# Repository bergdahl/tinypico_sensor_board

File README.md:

# tinypico_sensor_board

This is a small motherboard for the TinyPICO to connect sensors to a QWIIC/STEMMA QT or Grove connector.

It supports three different configurations for the voltage on the connectors, to suppport the maximum number of sensors.

 - 3.3V power - 3.3V signal
 - 5V power, 3.3V signal
 - 5V power, 5V signal

See the PDF file for configuration options.

# Schema

See the PDF file for schematics.

# PCB

Designfiles in EAGLE format can be found in the `PCB` folder. Gerber files can be found in the `PCB/Gerbers` folder.

# Firmwares

Firmware for connecting the sensors to MQTT is present in the `firmware` folder.

TODO: Add more firmware.

## Connectors

The QWIIC/Stemma QT port is connected to the default I2C pins of the TinyPICO, GPIO21 and GPIO22. 

The Grove connector is connected to GPIO4 and GPIO5, so to use I2C you need initialize it with `Wire.Begin(5, 4)`.

Note that the ESP32 allows you to assign any function to any pin, so any communication type is possible, like UART.

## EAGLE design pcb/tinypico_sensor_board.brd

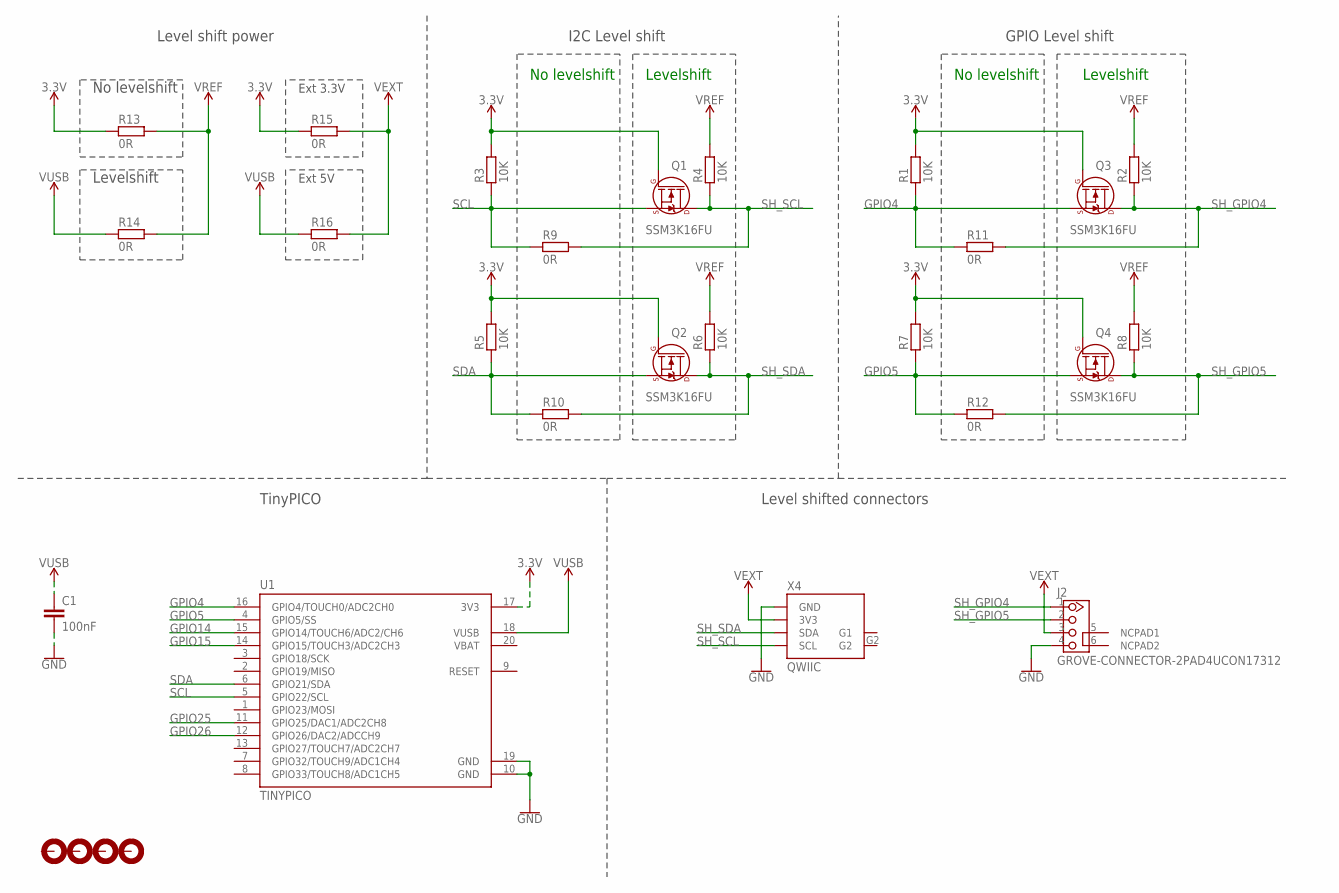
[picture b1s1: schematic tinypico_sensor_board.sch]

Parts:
C1: 100nF; C0603
H1, H2, H3, H4: MOUNTHOLE-PAD3.2; 3.2-PAD
J2: GROVE-CONNECTOR-2PAD4UCON17312; 4UCON17312
Q1, Q2, Q3, Q4: SSM3K16FU; SOT323
R1, R2, R3, R4, R5, R6, R7, R8: 10K; R0603
R9, R10, R11, R12: 0R; R0603
R13, R14, R15, R16: 0R; R1206
U1: TINYPICO
X4: QWIIC; JST-SH-4-SMD-RA

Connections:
3.3V: Q1.1 (G), Q2.1 (G), Q3.1 (G), Q4.1 (G), R1.2, R3.2, R5.2, R7.2, R13.1, R15.1, U1.17 (3V3)
GND: C1.2, J2.4 (GND), U1.10 (GND), U1.19 (GND), X4.GND
GPIO4: Q3.2 (S), R1.1, R11.1, U1.16 (GPIO4/TOUCH0/ADC2CH0)
GPIO5: Q4.2 (S), R7.1, R12.1, U1.4 (GPIO5/SS)
GPIO14: U1.15 (GPIO14/TOUCH6/ADC2/CH6)
GPIO15: U1.14 (GPIO15/TOUCH3/ADC2CH3)
GPIO25: U1.11 (GPIO25/DAC1/ADC2CH8)
GPIO26: U1.12 (GPIO26/DAC2/ADCCH9)
SCL: Q1.2 (S), R3.1, R9.1, U1.5 (GPIO22/SCL)
SDA: Q2.2 (S), R5.1, R10.1, U1.6 (GPIO21/SDA)
SH_GPIO4: J2.1 (SCL), Q3.3 (D), R2.1, R11.2
SH_GPIO5: J2.2 (SDA), Q4.3 (D), R8.1, R12.2
SH_SCL: Q1.3 (D), R4.1, R9.2, X4.SCL
SH_SDA: Q2.3 (D), R6.1, R10.2, X4.SDA
VEXT: J2.3 (VCC), R15.2, R16.2, X4.3V3
VREF: R2.2, R4.2, R6.2, R8.2, R13.2, R14.2
VUSB: C1.1, R14.1, R16.1, U1.18 (VUSB)

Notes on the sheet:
TinyPICO
No levelshift
Levelshift
I2C Level shift
GPIO Level shift
Level shift power
Level shifted connectors
Ext 3.3V
Ext 5V

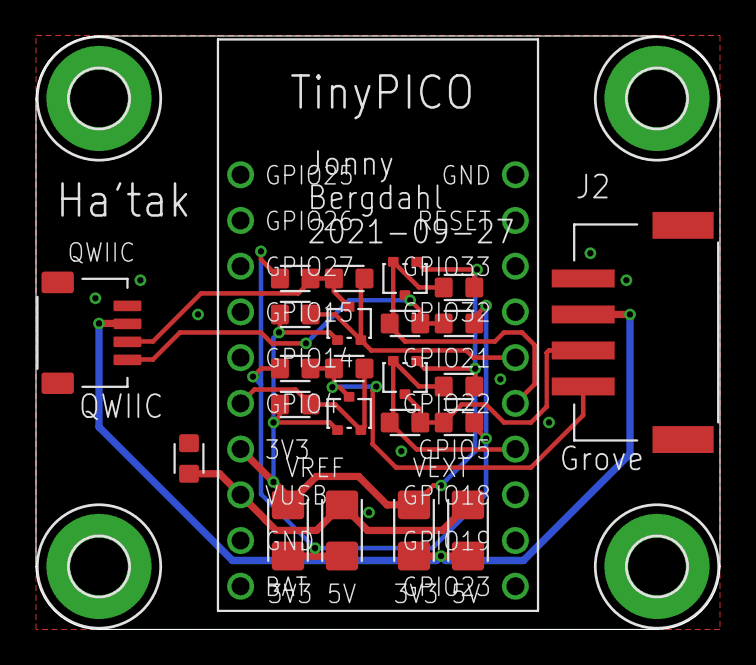
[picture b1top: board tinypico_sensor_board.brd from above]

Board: 2 copper layers, 38.0 x 33.0 mm, 28 parts (0 on the bottom side), 13 nets.

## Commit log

2021-11-03 Final version of PCB
2021-11-03 Updated Gerber files
